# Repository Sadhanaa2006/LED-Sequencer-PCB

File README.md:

**💡 555 Timer LED Sequencer | PCB Layout Design using Autodesk EAGLE**

**📖 Overview**

Designed a single-layer PCB for a 555 Timer-based LED Sequencer using Autodesk EAGLE from a provided schematic. The project involved component placement, manual trace routing, and PCB layout development to create a manufacturable design. The circuit generates sequential LED illumination using a NE555 Timer and CD4017 Decade Counter.

**✨ Features**

- ✅ Single-layer PCB layout
- ✅ Manual component placement
- ✅ Manual trace routing
- ✅ Sequential LED indication
- ✅ Through-hole PCB design
- ✅ Compact PCB layout

**⚙️ Working Principle**

- The **NE555 Timer** operates in astable mode to generate clock pulses.
- The **CD4017 Decade Counter** receives these pulses and activates one LED output at a time.
- Each clock pulse advances the sequence, creating a running LED effect.
- The sequence repeats continuously, producing a visually appealing LED pattern.

**🛠️ Components Used**

- NE555 Timer IC
- CD4017 Decade Counter IC
- LEDs
- Resistors
- Capacitors
- 9V Battery Connector

**💻 Software Used**

- Autodesk EAGLE

**🎯 Skills Demonstrated**

- PCB Layout Design
- Schematic Interpretation
- Component Placement
- Manual PCB Routing
- Through-Hole PCB Design
- PCB Documentation

**🎯 Applications**

- LED chaser circuits
- Decorative lighting systems
- Sequential display systems
- Educational electronics projects
- Digital timing demonstrations

**📌 Note**

The circuit schematic was provided as part of a PCB design exercise. This repository showcases the complete PCB layout process, including component placement, manual routing, and documentation using Autodesk EAGLE.

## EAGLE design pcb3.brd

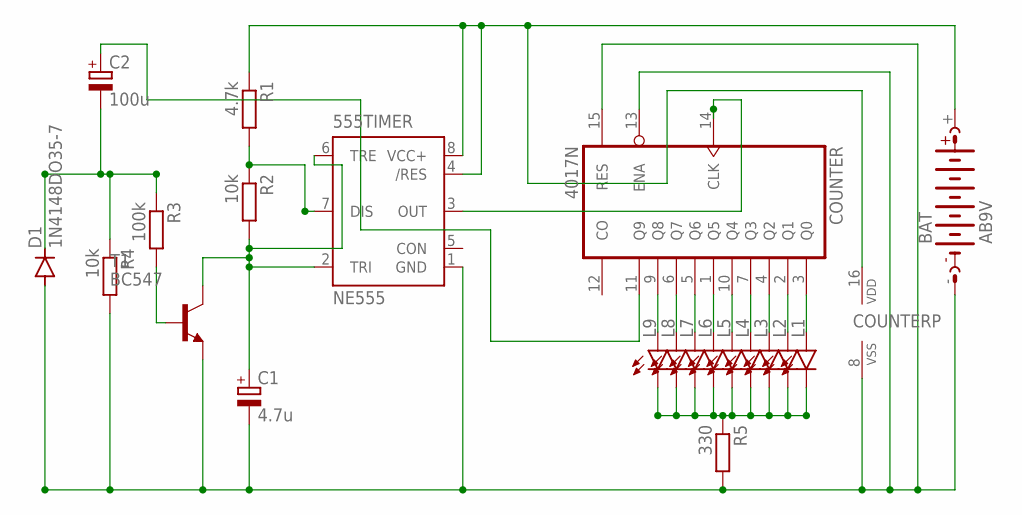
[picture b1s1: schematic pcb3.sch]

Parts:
555TIMER: NE555; DIL-08
BAT: AB9V
C1: 4.7u; E2,5-5
C2: 100u; E2,5-5
COUNTER: 4017N; DIL16
D1: 1N4148DO35-7; DO35-7
L1, L2, L3, L4, L5, L6, L7, L8, L9: LED5MM
R1: 4.7k; 0207/10
R2, R4: 10k; 0207/10
R3: 100k; 0207/10
R5: 330; 0207/10
T1: BC547; TO92

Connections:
unnamed: 555TIMER.7 (DIS), R1.2, R2.1
unnamed: 555TIMER.1 (GND), BAT.-, C1.-, COUNTER.8 (VSS), COUNTER.13 (ENA), COUNTER.15 (RES), D1.A, R4.2, R5.2, T1.1 (E)
unnamed: R3.2, T1.2 (B)
unnamed: 555TIMER.2 (TRI), 555TIMER.6 (TRE), C1.+, R2.2, T1.3 (C)
unnamed: C2.+, COUNTER.11 (Q9)
unnamed: C2.-, D1.C, R3.1, R4.1
unnamed: COUNTER.9 (Q8), L9.A
unnamed: COUNTER.6 (Q7), L8.A
unnamed: COUNTER.5 (Q6), L7.A
unnamed: COUNTER.1 (Q5), L6.A
unnamed: COUNTER.10 (Q4), L5.A
unnamed: COUNTER.7 (Q3), L4.A
unnamed: COUNTER.4 (Q2), L3.A
unnamed: COUNTER.2 (Q1), L2.A
unnamed: COUNTER.3 (Q0), L1.A
unnamed: L1.K (C), L2.K (C), L3.K (C), L4.K (C), L5.K (C), L6.K (C), L7.K (C), L8.K (C), L9.K (C), R5.1
unnamed: 555TIMER.3 (OUT), COUNTER.14 (CLK)
unnamed: 555TIMER.4 (/RES), 555TIMER.8 (VCC+), BAT.+, COUNTER.16 (VDD), R1.1

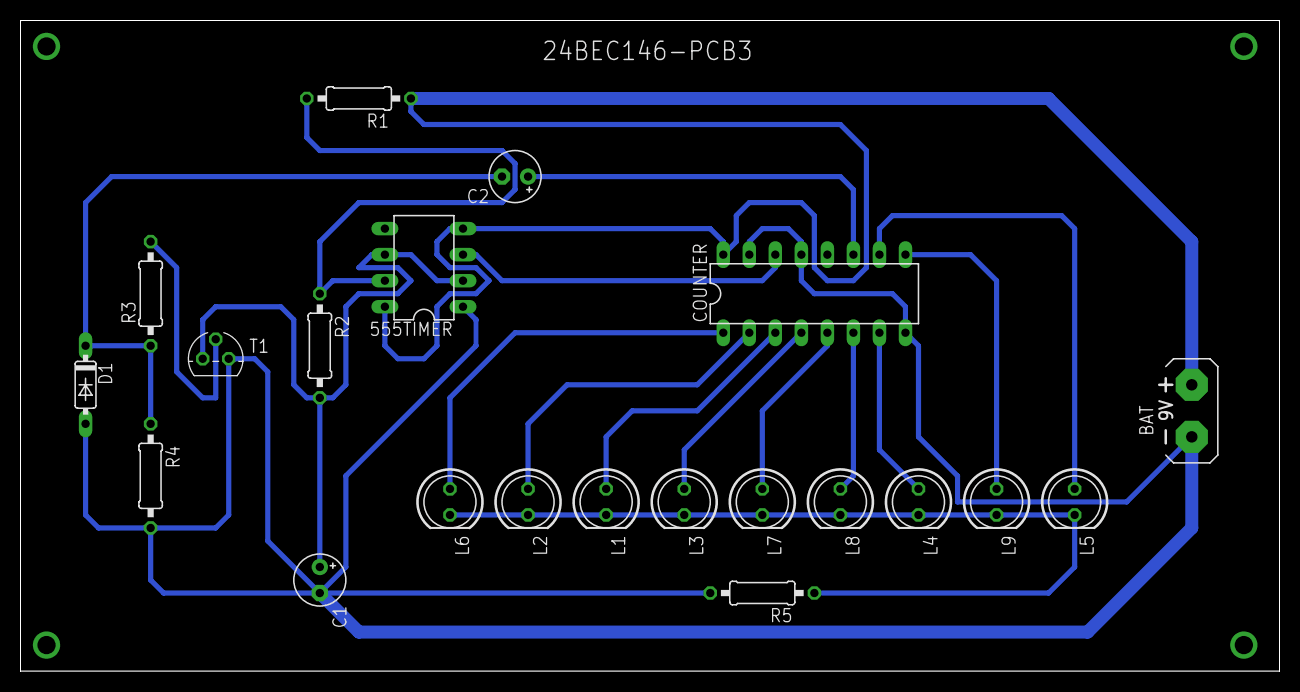
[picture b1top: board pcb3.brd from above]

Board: 2 copper layers, 122.9 x 63.5 mm, 21 parts (0 on the bottom side), 18 nets.

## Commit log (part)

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2026-06-20 Rename Schematic.png to Images/Schematic.png
2026-06-20 Rename Bottom Layer.png to Images/Bottom Layer.png
2026-06-20 Rename PCB design.png to Images/PCB design.png
2026-06-20 Rename Top Layer.png to Images/Top Layer.png
2026-06-20 Rename Top Layer.png to TopLayer.png
2026-06-20 Rename Bottom Layer.png to BottomLayer.png
2026-06-20 Rename PCB design.png to PCBdesign.png
